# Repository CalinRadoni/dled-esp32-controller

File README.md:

# ESP32 controller for digital LEDs

## Note

This repository is archived because I am building a version with better integration
in the [pax-devices](https://github.com/CalinRadoni/pax-devices) repository.

## Description

Efficiency, hardware control for digital LEDs and Wi-Fi communications - these are just some of the caracteristics of this controller.

It is designed to control digital LEDS like:

- WS2812, WS2812B, ... (*aka* NeoPixel) and derivatives like SK6812
- APA102 (*aka* DotStar) and derivatives like SK9822

## Features

- using the ESP32's RMT peripheral, the controller is able to drive two strips of digital LEDs like: WS2812, WS2812B, WS2812C, WS2812S, WS2813, WS2815, WS2812D, etc.
- using the ESP32's HSPI peripheral, the controller is able to drive a strip of digital LEDs like APA102
- two *real* logic level shifter circuits
- the power supply for LEDs is controlled using a Power MOSFET
- I2C and two general-purpose extension headers
- high efficiency synchronous buck converter
- supply voltage supervisor

## Software

My [esp32_digitalLEDs](https://github.com/CalinRadoni/esp32_digitalLEDs) repository contains code to use the ESP32's RMT peripheral to drive digital LEDs.

The code dedicated to this board is not yet built.

## Development Environment

Operating system is [Debian](https://www.debian.org/)

Tools:

- [KiCad EDA](http://kicad-pcb.org/)
- [Visual Studio Code](https://code.visualstudio.com/)
- [Git](https://git-scm.com/)
- [GIMP](https://www.gimp.org/)
- [Inkscape](https://inkscape.org/en/)

## Versions

### Version 1

- *Fab* files are moved to the Fab-v1 directory
- Gerbers and drill files are sent to SeeedStudio for PCB fabrication
- BOM is in the making and components have to be sourced
- I should start to write some software

### Version 0.x

Hardware revision 10 is presented in the following rendered picture:

Hardware revision 9 is presented in the following rendered picture:

Hardware revision 8 is presented in the following rendered picture:

## License

The software and documentation are released under the [GNU GPLv3](http://www.gnu.org/licenses/gpl-3.0.html) License. See the __LICENSE-GPLv3.txt__ file.

The hardware schematics are licensed under a [Creative Commons Attribution-ShareAlike 4.0 International License](http://creativecommons.org/licenses/by-sa/4.0/).
See the __LICENSE-CC-BY-SA-4.0.txt__ file.

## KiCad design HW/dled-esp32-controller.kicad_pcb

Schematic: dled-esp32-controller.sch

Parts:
C1, C2, C5, C6, C9: 100nF; C0805HS; part-number CL21B104KBCNNNC
C3: 10uF; C0805HS; part-number CL21B106KQQNNNE
C4: 100nF-NC; C0805HS; part-number DNP
C7: 10uF/10V/1mOhm; C0805HS; part-number EMK212BB7106KG-T
C8: 22uF/6.3V/1mOhm; C0805HS; part-number JMK212BJ226MG-T
D1: LED; LED1206; part-number OF-SMD3216B
H1, H2: Hole; HoleNPT-M3; part-number DNP
J1: CS_4; Pin_Header_Straight_1x04
J2: CS_3; Pin_Header_Straight_1x03_Cyan
J3, J4: CS_2; Pin_Header_Straight_1x02
J5: CS_3; Pin_Header_Straight_1x03_Yellow
J6: CS_5; Pin_Header_Straight_1x05; part-number DNP
J7: CS_3; Pin_Header_Straight_1x03; part-number DNP
J8, J9: CS_Pwr; DG301-5-2
L1: 2.2uH; ASPI-0530HI; part-number ASPI-0530HI-2R2M-T2
Q1: STD46P4LLF6; TO-252; part-number STD46P4LLF6
Q2: IRLML2502; SOT-23-GSD-HS; part-number IRLML2502GPbF
R1, R8: 10k; R0805HS; part-number CRCW080510K0FKEA
R2, R5, R9, R10: 330; R0805HS; part-number CRCW0805330RFKTABC
R3, R4: 2k2; R0805HS; part-number ERJ6ENF2001V
R6: 442k 1%; R0805HS; part-number ERJ-6ENF4423V
R7: 100k 1%; R0805HS; part-number ERJ-6ENF1003V
SYM1: Open Source Hardware; OSHW-Logo_5.7x6mm_SilkScreen; part-number DNP
U1: ESP-WROOM-32; ESP-WROOM-32-HandSolder; part-number ESP32-WROOM-32
U2: BD48K28...30; SOT-23-HS; part-number BD48K
U3: TLV62569DBV; SOT-23-5-HS; part-number TLV62569DBV
U4, U5: SN74LV1T34; SOT-23-5-HS; part-number SN74LV1T34DBVR

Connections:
+3V3: C2.1, C3.1, C8.1, J1.1, J6.5, J7.1, L1.2, R1.1, R3.2, R4.2, R6.1, U1.2 (3V3), U2.3 (VDD)
+5V: C6.1, C7.1, J9.1, Q1.3, R8.1, U3.1 (EN), U3.4 (VIN)
+5VL: C5.1, C9.1, J8.2, Q1.2, U4.5 (Vcc), U5.5 (Vcc)
/25: J6.4, U1.10 (IO25)
/32: J6.2, U1.8 (IO32)
/33: J6.3, U1.9 (IO33)
/Boot: C4.1, J3.1, U1.25 (IO0)
/IO4: J7.2, U1.26 (IO4)
/LEDc1: U1.13 (IO14), U4.2 (A)
/LEDc2: U1.16 (IO13), U5.2 (A)
/LEDo1: J5.1, R5.1
/LEDo2: J5.3, R10.1
/Reset: C1.1, J4.1, R1.2, U1.3 (EN), U2.2 (OUT)
/SCL: J1.3, R4.1, U1.36 (IO22)
/SDA: J1.4, R3.1, U1.33 (IO21)
/SPSW: L1.1, U3.3 (SW)
/U0RXD: J2.2, U1.34 (RXD0)
/U0TXD: J2.1, U1.35 (TXD0)
/extPwr: R9.2, U1.11 (IO26)
GND: C1.2, C2.2, C3.2, C4.2, C5.2, C6.2, C7.2, C8.2, C9.2, D1.K, J1.2, J2.3, J3.2, J4.2, J5.2, J6.1, J7.3, J8.1, J9.2, Q2.S, R7.1, U1.1 (Gnd), U1.15 (Gnd), U1.38 (Gnd), U1.39 (Gnd), U2.1 (GND), U3.2 (GND), U4.3 (Gnd), U5.3 (Gnd)
unnamed: D1.A, R2.1
unnamed: Q1.1, Q2.D, R8.2
unnamed: Q2.G, R9.1
unnamed: R2.2, U1.24 (IO2)
unnamed: R5.2, U4.4 (Y)
unnamed: R6.2, R7.2, U3.5 (FB)
unnamed: R10.2, U5.4 (Y)

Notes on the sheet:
Mounting holes spaced at 44,5 mm for compatibility with MeanWell EPS 25/35/45S/65S power sources.

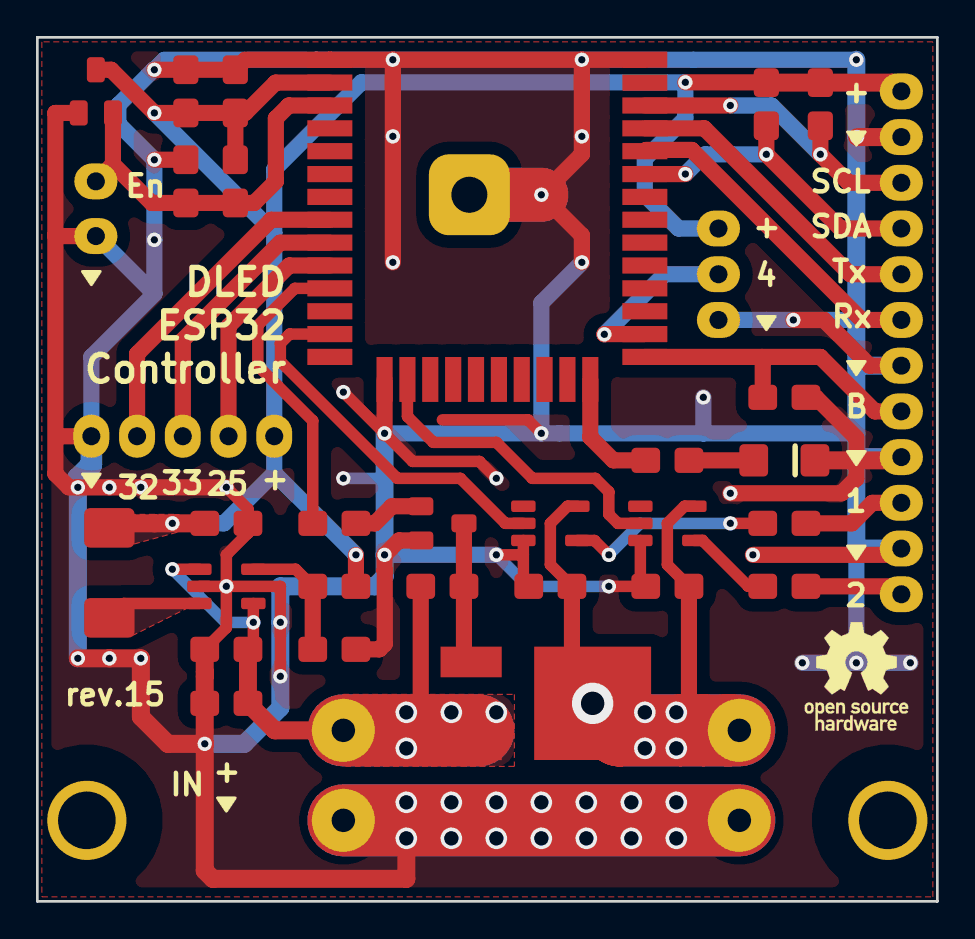
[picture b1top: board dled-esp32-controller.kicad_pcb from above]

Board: 2 copper layers, 50.0 x 48.0 mm, 40 parts (0 on the bottom side), 27 nets.

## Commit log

2019-03-19 Modifies the design for two outputs
2019-03-22 Updates README.md for version 0.7
2019-03-25 Adds an extension header and improves many PCB traces.
2019-03-26 Updates README.md for version 0.8
2019-03-27 Modifies the schematic to add a second extension connector
2019-03-27 Rebuilds the PCB for the second extension connector
2019-03-28 Adjusts the labels for extension connectors
2019-03-31 Adds revision info for PCB and updates README.md for version 0.9
2019-04-02 Changes the 3D representation of some connectors
2019-04-02 Updates for version 0.10
2019-04-04 Changes the inductor to a more correct value and the LED's resistor to a sane value
2019-04-04 Rebuilds the PCB for revision 11
2019-04-04 Updates README.md for version 0.11
2019-04-30 Updates components to add manufacturer, part number, ... fields, checked the values and adds power flags for a clean ERC test
2019-05-01 Changes the C4 to NC and removes the keepout areas from under ESP32 module, as in Espressif's DevKitC v4
2019-05-07 Improves component placement for ESP's power and reset circuitry.
2019-05-09 Creates the files for PCB fabrication, and adjusts the PCB layout a little.
2019-05-11 Finishes the files for PCB fabrication and move them to Fab-v1 directory.
2019-05-18 Updates some part numbers.
2019-09-22 Archiving the repository
